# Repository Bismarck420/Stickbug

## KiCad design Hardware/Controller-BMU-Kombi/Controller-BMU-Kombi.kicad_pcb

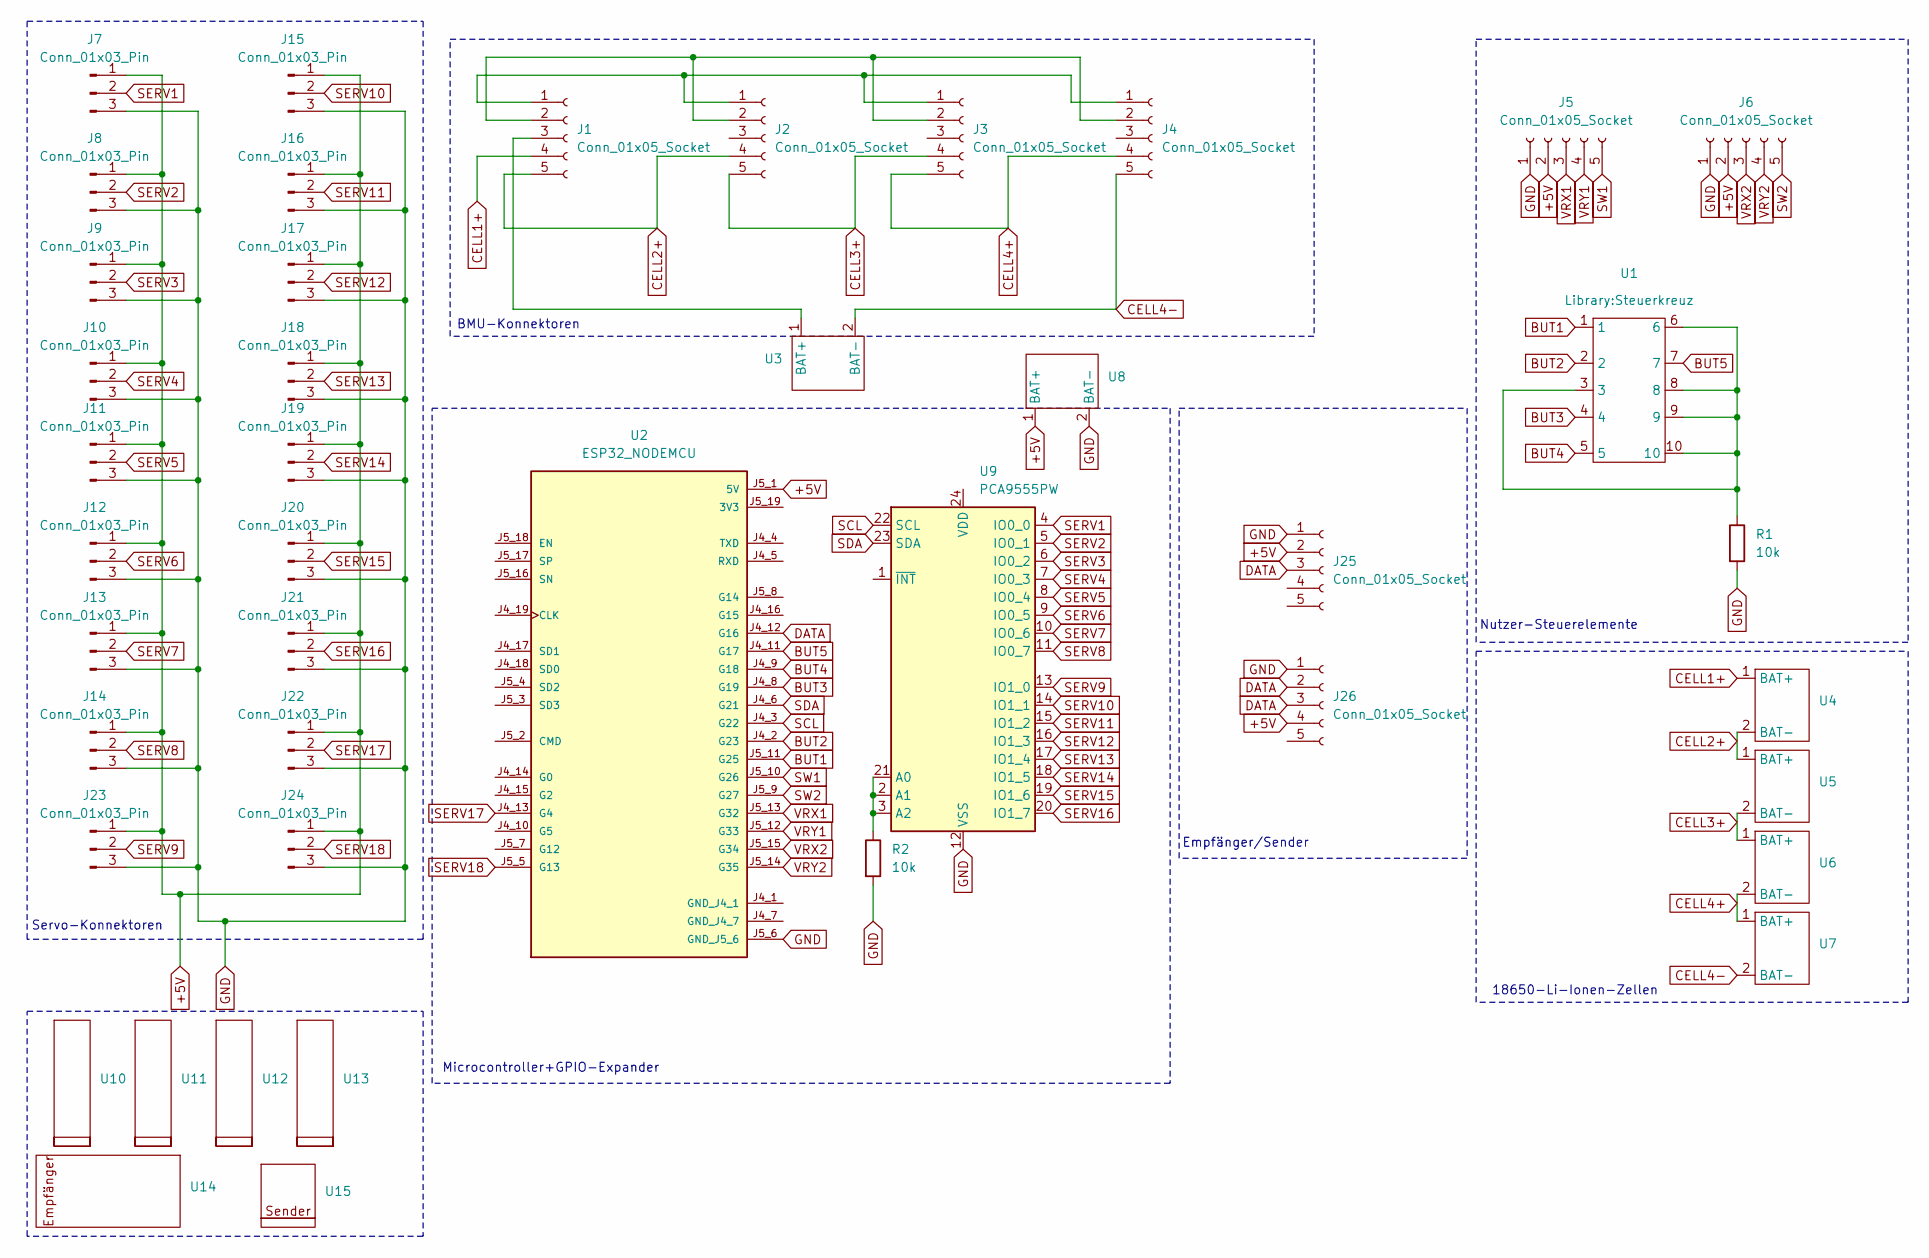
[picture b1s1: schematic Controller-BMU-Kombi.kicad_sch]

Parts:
J1, J2, J3, J4, J5, J6, J25, J26: Conn_01x05_Socket; PinSocket_1x05_P2.54mm_Horizontal
J7, J8, J9, J10, J11, J12, J13, J14, J15, J16, J17, J18, J19, J20, J21, J22, J23, J24: Conn_01x03_Pin; PinHeader_1x03_P2.54mm_Vertical
R1, R2: 10k; R_1206_3216Metric
U1: Steuerkreuz
U2: ESP32_NODEMCU; MODULE_ESP32_NODEMCU
U3, U4, U5, U6, U7, U8: Batteriestecker
U9: PCA9555PW; TSSOP-24_4.4x7.8mm_P0.65mm
U10, U11, U12, U13: BMU
U14: Empfänger
U15: Sender

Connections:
+5V: J5.2, J6.2, J7.1, J8.1, J9.1, J10.1, J11.1, J12.1, J13.1, J14.1, J15.1, J16.1, J17.1, J18.1, J19.1, J20.1, J21.1, J22.1, J23.1, J24.1, J25.2, J26.4, U2.J5_1 (5V), U8.1 (BAT+)
BUT1: U1.1, U2.J5_11 (G25)
BUT2: U1.2, U2.J4_2 (G23)
BUT3: U1.4, U2.J4_8 (G19)
BUT4: U1.5, U2.J4_9 (G18)
BUT5: U1.7, U2.J4_11 (G17)
CELL1+: J1.4, U4.1 (BAT+)
CELL2+: J1.5, J2.4, U4.2 (BAT-), U5.1 (BAT+)
CELL3+: J2.5, J3.4, U5.2 (BAT-), U6.1 (BAT+)
CELL4+: J3.5, J4.4, U6.2 (BAT-), U7.1 (BAT+)
CELL4-: J4.5, U3.2 (BAT-), U7.2 (BAT-)
DATA: J25.3, J26.2, J26.3, U2.J4_12 (G16)
GND: J5.1, J6.1, J7.3, J8.3, J9.3, J10.3, J11.3, J12.3, J13.3, J14.3, J15.3, J16.3, J17.3, J18.3, J19.3, J20.3, J21.3, J22.3, J23.3, J24.3, J25.1, J26.1, R1.2, R2.2, U2.J5_6 (GND_J5_6), U8.2 (BAT-), U9.12 (VSS)
unnamed: J1.1, J2.1, J3.1, J4.1
unnamed: J1.2, J2.2, J3.2, J4.2
unnamed: J1.3, U3.1 (BAT+)
unnamed: R1.1, U1.3, U1.6, U1.8, U1.9, U1.10
unnamed: R2.1, U9.2 (A1), U9.3 (A2), U9.21 (A0)
SCL: U2.J4_3 (G22), U9.22 (SCL)
SDA: U2.J4_6 (G21), U9.23 (SDA)
SERV1: J7.2, U9.4 (IO0_0)
SERV2: J8.2, U9.5 (IO0_1)
SERV3: J9.2, U9.6 (IO0_2)
SERV4: J10.2, U9.7 (IO0_3)
SERV5: J11.2, U9.8 (IO0_4)
SERV6: J12.2, U9.9 (IO0_5)
SERV7: J13.2, U9.10 (IO0_6)
SERV8: J14.2, U9.11 (IO0_7)
SERV9: J23.2, U9.13 (IO1_0)
SERV10: J15.2, U9.14 (IO1_1)
SERV11: J16.2, U9.15 (IO1_2)
SERV12: J17.2, U9.16 (IO1_3)
SERV13: J18.2, U9.17 (IO1_4)
SERV14: J19.2, U9.18 (IO1_5)
SERV15: J20.2, U9.19 (IO1_6)
SERV16: J21.2, U9.20 (IO1_7)
SERV17: J22.2, U2.J4_13 (G4)
SERV18: J24.2, U2.J5_5 (G13)
SW1: J5.5, U2.J5_10 (G26)
SW2: J6.5, U2.J5_9 (G27)
VRX1: J5.3, U2.J5_13 (G32)
VRX2: J6.3, U2.J5_15 (G34)
VRY1: J5.4, U2.J5_12 (G33)
VRY2: J6.4, U2.J5_14 (G35)

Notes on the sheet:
Nutzer-Steuerelemente
Microcontroller+GPIO-Expander
Empfänger/Sender
Servo-Konnektoren
BMU-Konnektoren
18650-Li-Ionen-Zellen

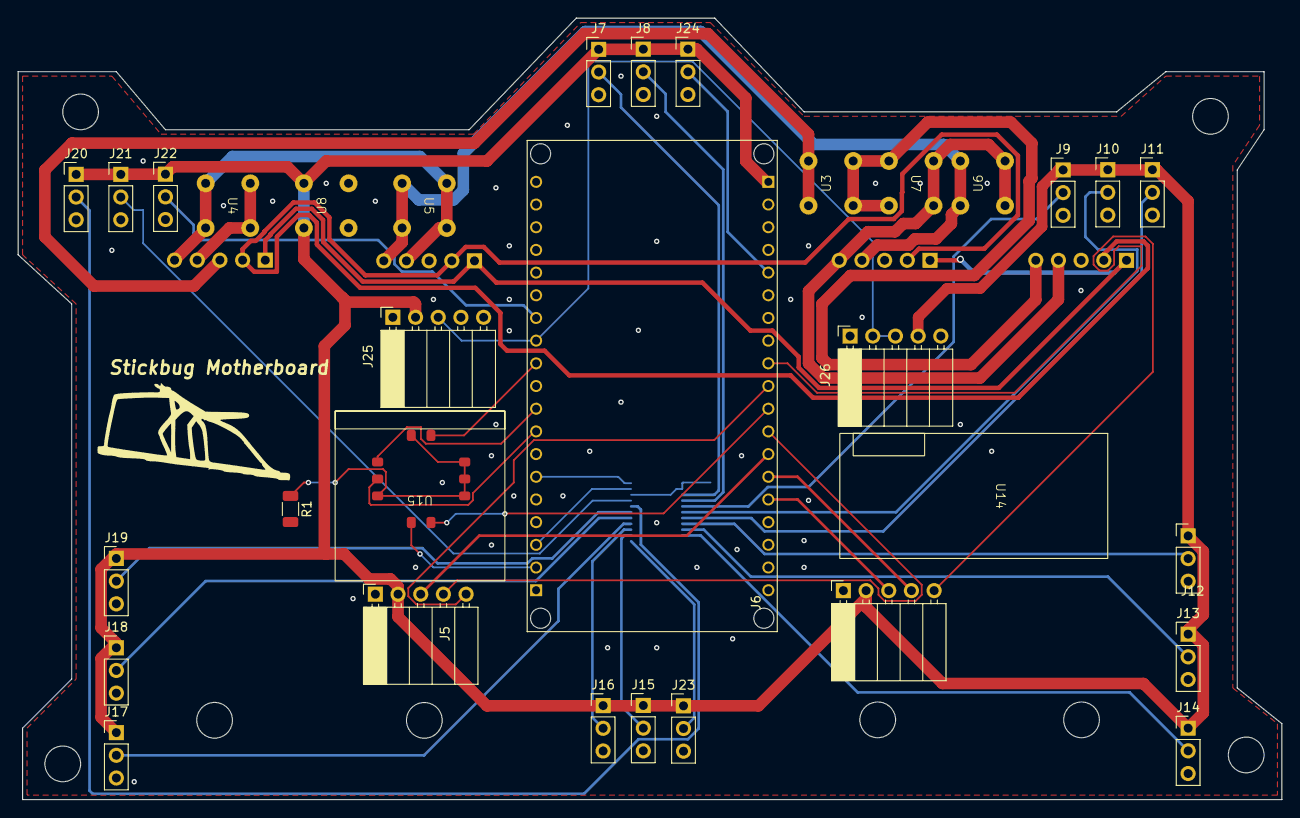
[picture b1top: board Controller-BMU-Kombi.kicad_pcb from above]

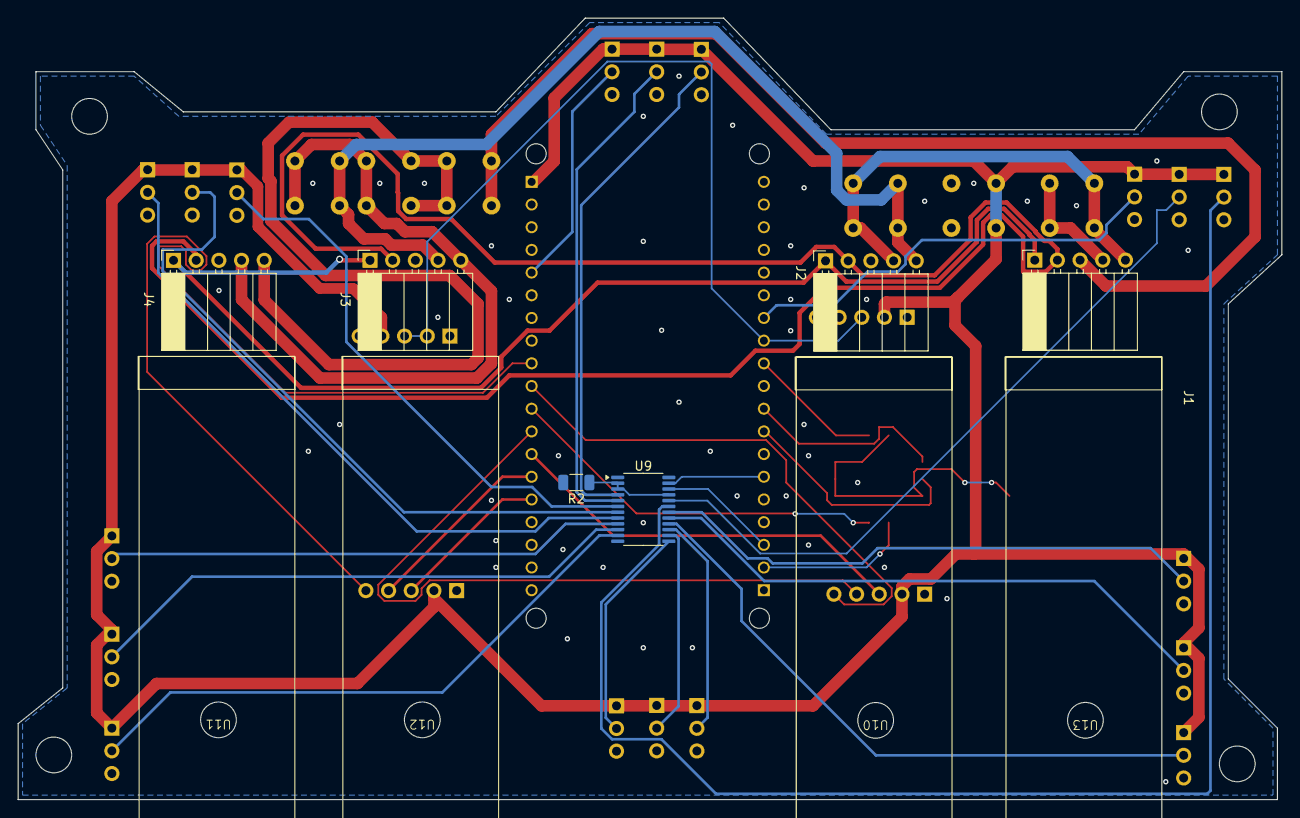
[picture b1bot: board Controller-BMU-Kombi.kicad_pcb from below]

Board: 2 copper layers, 141.5 x 87.5 mm, 43 parts (10 on the bottom side), 44 nets.

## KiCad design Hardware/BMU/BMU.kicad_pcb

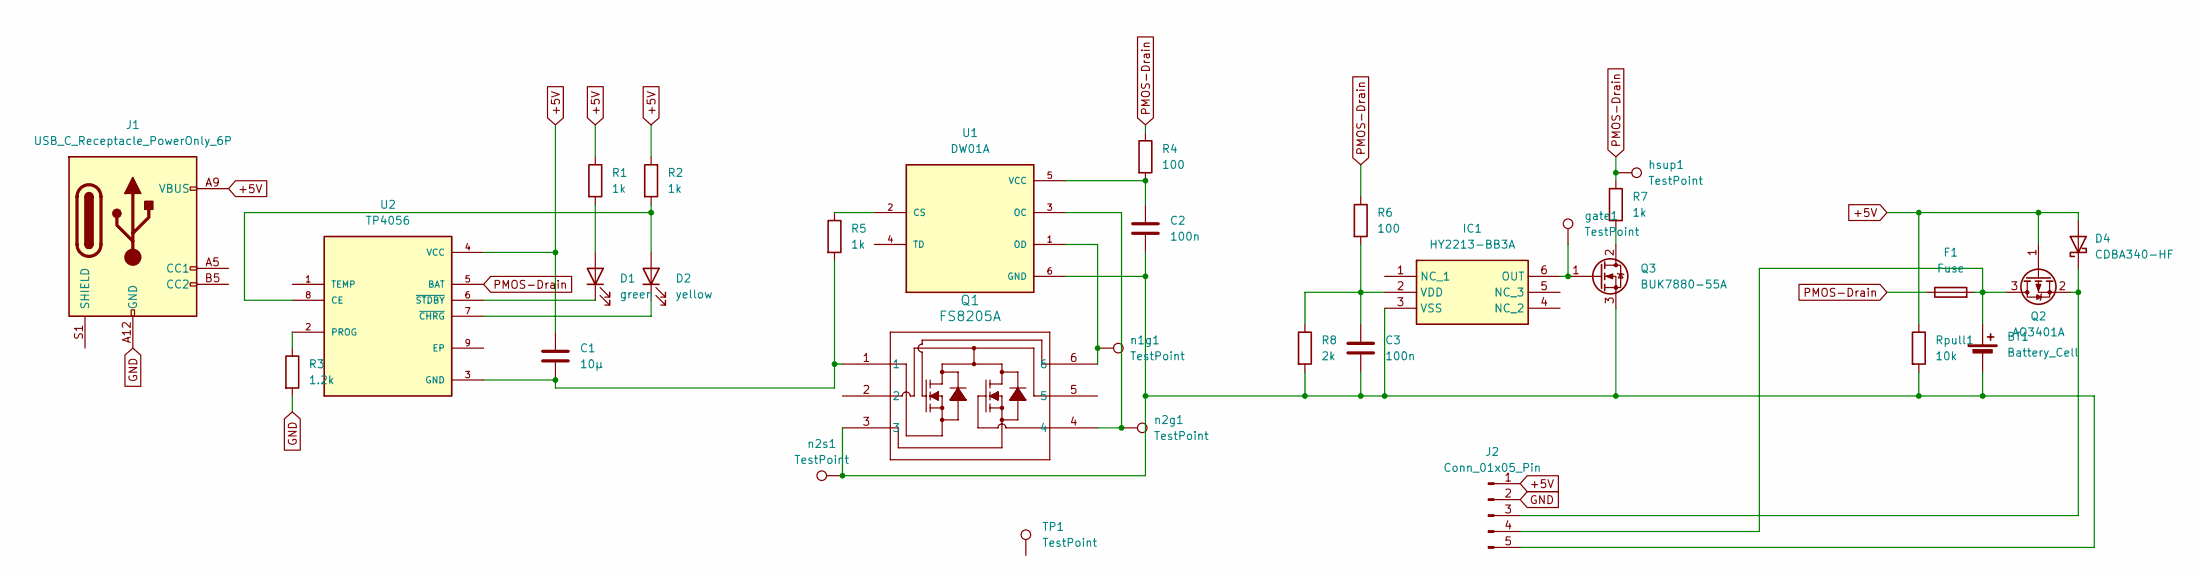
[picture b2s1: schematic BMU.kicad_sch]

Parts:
BT1: Battery_Cell
C1: 10µ; C_1206_3216Metric
C2, C3: 100n; C_1206_3216Metric
D1: green; LED_1206_3216Metric
D2: yellow; LED_1206_3216Metric
D4: CDBA340-HF; D_SMA
F1: Fuse; Fuse_1206_3216Metric
IC1: HY2213-BB3A; SOT95P280X140-6N; Manufacturer_Part_Number HY2213-BB3A
J1: USB_C_Receptacle_PowerOnly_6P; USB_C_Receptacle_GCT_USB4125-xx-x_6P_TopMnt_Horizontal
J2: Conn_01x05_Pin; PinHeader_1x05_P2.54mm_Horizontal
Q1: FS8205A; SOT-23-6L_TCP
Q2: AO3401A; SOT-23
Q3: BUK7880-55A; SOT-223-3_TabPin2
R1, R2, R5, R7: 1k; R_1206_3216Metric
R3: 1.2k; R_1206_3216Metric
R4, R6: 100; R_1206_3216Metric
R8: 2k; R_1206_3216Metric
Rpull1: 10k; R_1206_3216Metric
TP1: TestPoint; TestPoint_Plated_Hole_D2.0mm
U1: DW01A; SOT95P280X145-6N; PARTREV 1.8
U2: TP4056; SOP127P600X175-9N
gate1: TestPoint; Pin_D1.0mm_L10.0mm
hsup1: TestPoint; Pin_D1.0mm_L10.0mm
n1g1, n2g1, n2s1: TestPoint; Pin_D1.0mm_L10.0mm

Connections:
+5V: C1.1, D4.2 (A), J1.A9 (VBUS), J1.B9 (VBUS), J2.1, Q2.1 (G), R1.1, R2.1, Rpull1.1, U2.4 (VCC)
GND: J1.A12 (GND), J1.B12 (GND), J2.2, R3.2
unnamed: D1.2 (A), R1.2
unnamed: D1.1 (K), U2.6 (~STDBY)
unnamed: D2.2 (A), R2.2, U2.8 (CE)
unnamed: D2.1 (K), U2.7 (~CHRG)
unnamed: D4.1 (K), J2.3, Q2.2 (S)
unnamed: IC1.6 (OUT), Q3.1 (G), gate1.1
unnamed: C3.1, IC1.2 (VDD), R6.2, R8.1
unnamed: BT1.2 (-), C2.2, C3.2, IC1.3 (VSS), J2.5, Q1.3, Q3.3 (S), R8.2, Rpull1.2, U1.6 (GND), n2s1.1
unnamed: BT1.1 (+), F1.2, J2.4, Q2.3 (D)
unnamed: Q3.2 (D), R7.2
unnamed: R5.1, U1.2 (CS)
unnamed: Q1.4, U1.3 (OC), n2g1.1
unnamed: Q1.6, U1.1 (OD), n1g1.1
unnamed: C2.1, R4.2, U1.5 (VCC)
unnamed: C1.2, Q1.1, R5.2, U2.3 (GND)
unnamed: R3.1, U2.2 (PROG)
PMOS-Drain: F1.1, R4.1, R6.1, R7.1, U2.5 (BAT), hsup1.1

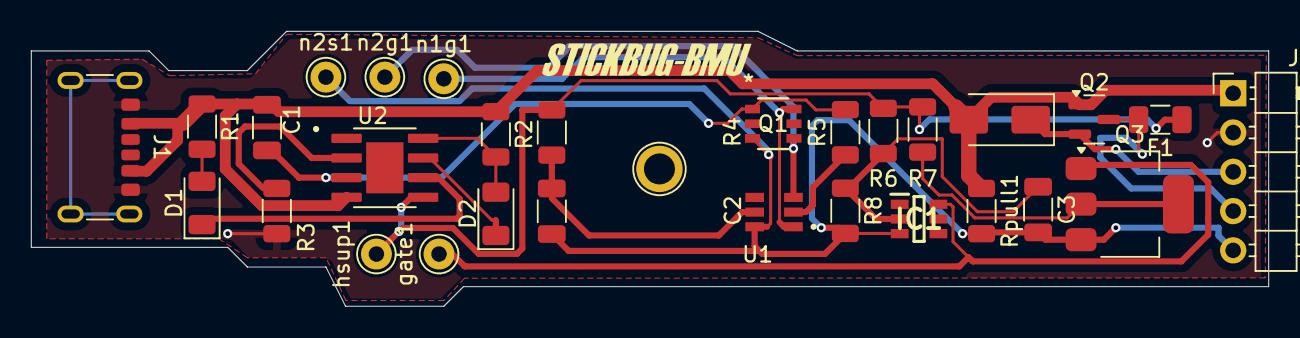
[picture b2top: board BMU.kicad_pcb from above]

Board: 2 copper layers, 80.0 x 17.8 mm, 30 parts (0 on the bottom side), 19 nets.

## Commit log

2024-10-22 Added all files
2024-10-22 Updated Document Hierarchy
2024-10-22 Updated BMU
2024-10-24 added circuitry for user controls
2024-10-24 synchronizing
2024-10-26 added servo connectors
2024-10-27 added gerber files
2024-10-29 added rf connectors, changed a few net labels
2024-10-30 general pcb layout
2024-11-01 Finished Controller-BMU-Kombi PCB
    routing finished + finishing touches applied
2024-11-03 final updates
2024-12-06 Updates before deletion
2025-03-22 Software
